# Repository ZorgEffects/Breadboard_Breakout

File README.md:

# Breadboard_Breakout
This is a PCB of a breakout audio board used for audio design on a breadboard.  
It's been made to align with a 1660pt breadboard like this one:  
https://mou.sr/4qExcgZ

# Features:
- 9v regulator. Can be turned off with a jumper.
- 3x jacks in/out/aux for audio/CVs
- Relay bypass between IN/OUT. The relay can be removed with jumper.
- 4x push switches with wiring connection
- 6x screw connectors to fix pots on the boards and wire them to the breadboard
- Filtered Vref = Vcc/2
- Bananas connexion for an external power supply
- Test points for signals (T1 and T2, near the bananas)
- Test points for I/Os (IN/OUT/AUX, right of the jacks)

# Short BOM:
Relay :  
https://www.mouser.fr/ProductDetail/Omron-Electronics/G6K-2P-Y-DC9?qs=wkx8pu8tL7LXpnqEum69xQ%3D%3D  
Push Switch (latch):  
https://www.mouser.fr/ProductDetail/E-Switch/JN2UOANAGX?qs=3Jlm%2Fl9ddLz4b5MH%2B0K8sg%3D%3D&countryCode=DE&currencyCode=EUR  
Switch cap:  
https://www.mouser.fr/ProductDetail/E-Switch/TAG-BLK?qs=sGAEpiMZZMtFyPk3yBMYYOwc5eDcStsDSmqEZ9eg82w%3D  
Pot connector:  
https://www.mouser.fr/ProductDetail/Phoenix-Contact/1935394?qs=%2FbRkJSLTVS%2FBYbus49HMUQ%3D%3D&countryCode=DE&currencyCode=EUR  
Bypass switch:  
https://www.mouser.fr/ProductDetail/Same-Sky/TS14-1212-100-BK-160-SCR-D?qs=t7xnP681wgUxNt1zer%2Bdww%3D%3D  
Jacks:  
https://www.mouser.fr/ProductDetail/Neutrik/NMJ4HCD2?qs=SzdD80gJ2cAr9Xh3wJi7nw%3D%3D  
Terminals 2.54:  
https://www.mouser.fr/ProductDetail/3M-Electronic-Solutions-Division/2324-6121TG?qs=bmCxD588tEjY10%2FzUyHH%2BQ%3D%3D  
https://www.mouser.fr/c/connectors/headers-wire-housings/?contact%20gender=Socket%20(Female)&mounting%20angle=Straight&mounting%20style=Through%20Hole&number%20of%20rows=1%20Row&pitch=2.54%20mm%20(0.1%20in)~~2.54%20mm%2C%205%20mm&row%20spacing=2.54%20mm%20(0.1%20in)&rp=connectors%2Fheaders-wire-housings%7C~Pitch  

The bananas plugs are these:  
https://www.microjpm.com/products/ad27504/

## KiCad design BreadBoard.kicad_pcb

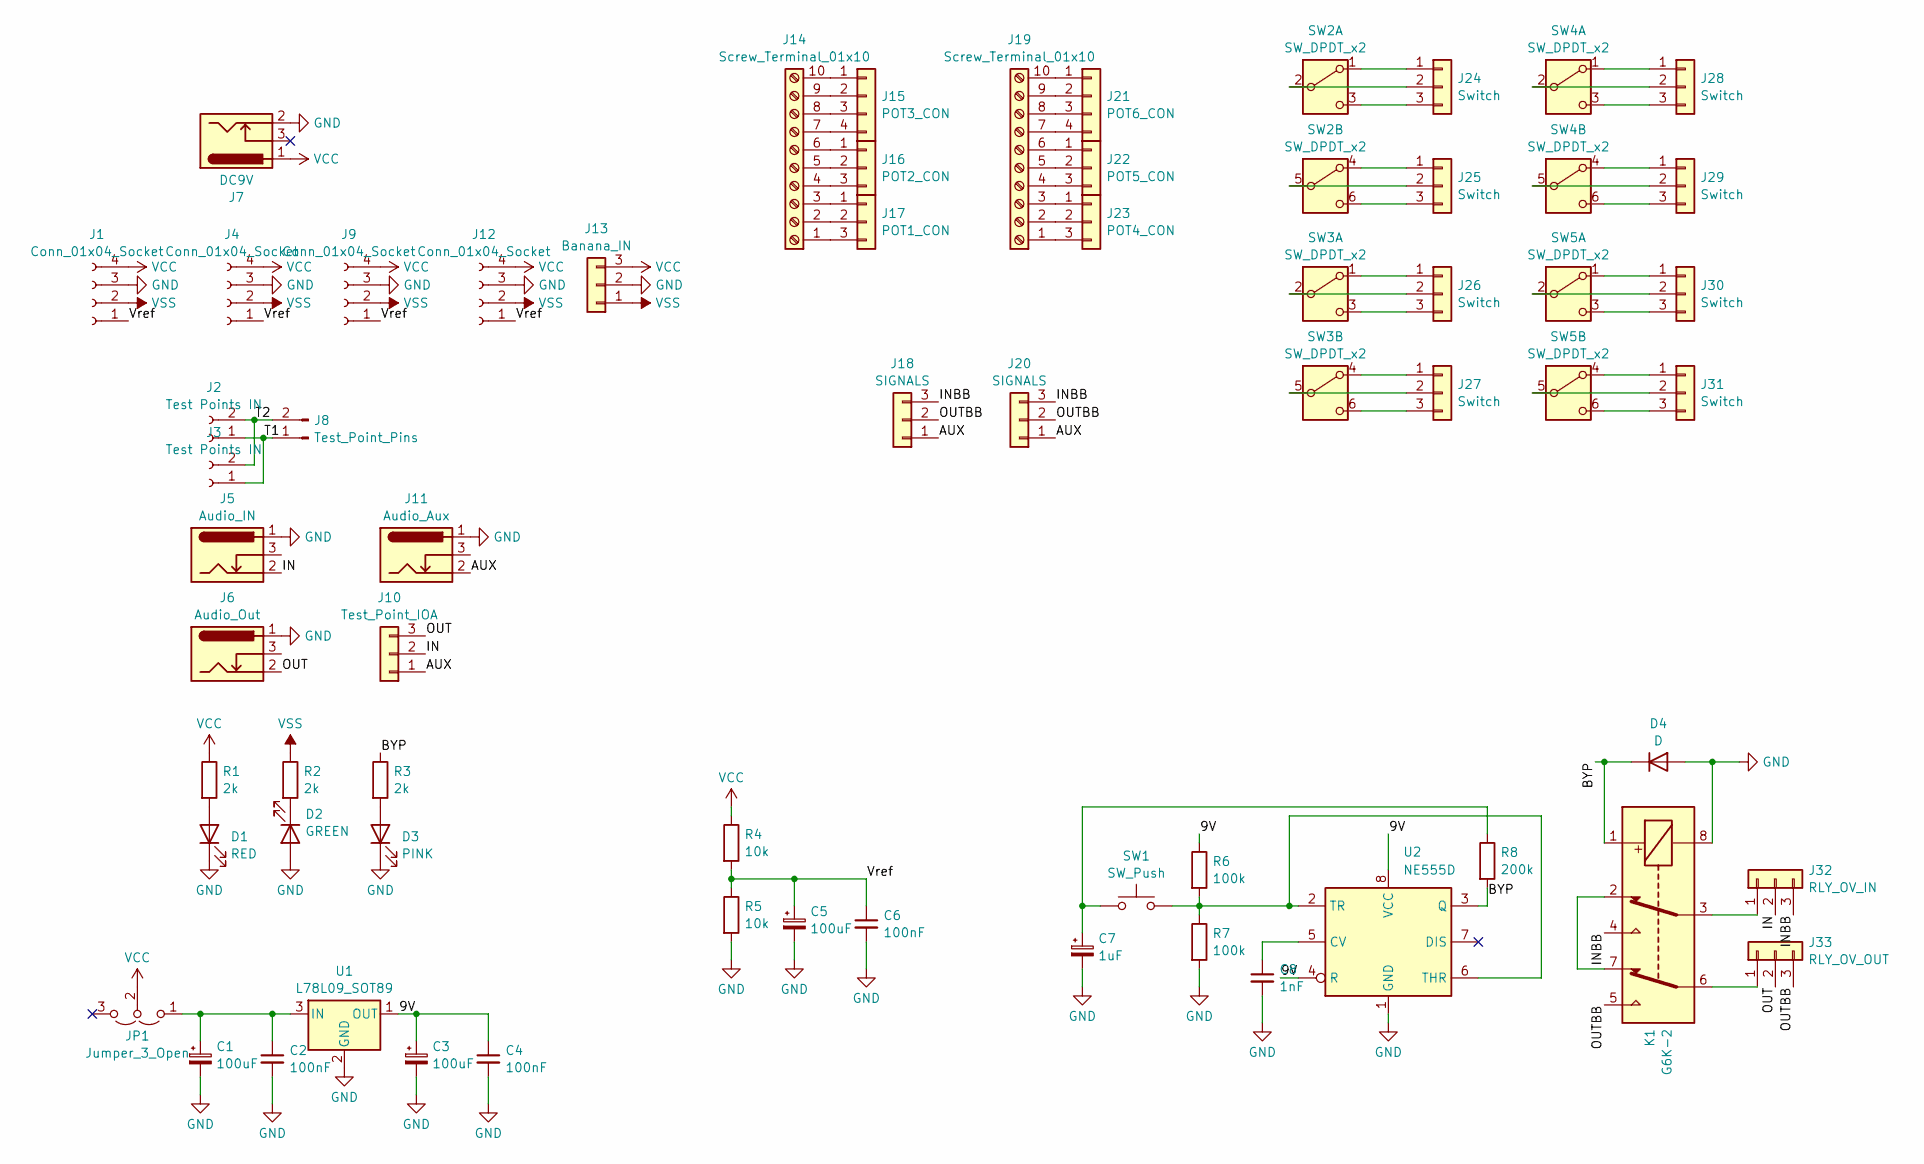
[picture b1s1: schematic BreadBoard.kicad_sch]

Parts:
C1, C3, C5: 100uF; CP_Radial_D6.3mm_P2.50mm
C2, C4, C6: 100nF; C_Rect_L7.0mm_W2.0mm_P5.00mm
C7: 1uF; CP_Radial_D4.0mm_P2.00mm
C8: 1nF; C_Rect_L7.0mm_W2.0mm_P5.00mm
D1: RED; LED_D5.0mm
D2: GREEN; LED_D5.0mm
D3: PINK; LED_D5.0mm
D4: D; D_A-405_P7.62mm_Horizontal
J1, J4, J9, J12: Conn_01x04_Socket; PinSocket_1x04_P2.54mm_Vertical
J2, J3: Test Points IN; PinSocket_1x02_P2.54mm_Vertical
J5: Audio_IN; Jack Neutrik Mono Pins SW
J6: Audio_Out; Jack Neutrik Mono Pins SW
J7: DC9V; Jack DC
J8: Test_Point_Pins; PinHeader_1x02_P2.54mm_Vertical
J10: Test_Point_IOA; PinHeader_1x03_P2.54mm_Vertical
J11: Audio_Aux; Jack Neutrik Mono Pins SW
J13: Banana_IN; PinHeader_1x03_P2.54mm_Vertical
J14, J19: Screw_Terminal_01x10; TerminalBlock_RND_205-00020_1x10_P5.00mm_Horizontal
J15: POT3_CON; PinSocket_1x04_P2.54mm_Vertical
J16: POT2_CON; PinSocket_1x03_P2.54mm_Vertical
J17: POT1_CON; PinSocket_1x03_P2.54mm_Vertical
J18, J20: SIGNALS; PinSocket_1x03_P2.54mm_Vertical
J21: POT6_CON; PinSocket_1x04_P2.54mm_Vertical
J22: POT5_CON; PinSocket_1x03_P2.54mm_Vertical
J23: POT4_CON; PinSocket_1x03_P2.54mm_Vertical
J24, J25, J26, J27, J28, J29, J30, J31: Switch; PinSocket_1x03_P2.54mm_Vertical
J32: RLY_OV_IN; PinHeader_1x03_P2.54mm_Vertical
J33: RLY_OV_OUT; PinHeader_1x03_P2.54mm_Vertical
JP1: Jumper_3_Open; PinHeader_1x03_P2.54mm_Vertical
K1: G6K-2; Relay_DPDT_Omron_G6K-2P-Y
R1, R2, R3: 2k; R_Axial_DIN0207_L6.3mm_D2.5mm_P10.16mm_Horizontal
R4, R5: 10k; R_Axial_DIN0207_L6.3mm_D2.5mm_P10.16mm_Horizontal
R6, R7: 100k; R_Axial_DIN0207_L6.3mm_D2.5mm_P10.16mm_Horizontal
R8: 200k; R_Axial_DIN0207_L6.3mm_D2.5mm_P10.16mm_Horizontal
SW1: SW_Push; SW_PUSH-12mm
SW2, SW3, SW4, SW5: SW_DPDT_x2; DPDT_ESwitch
U1: L78L09_SOT89; DPAK-3
U2: NE555D; SOIC-8_3.9x4.9mm_P1.27mm

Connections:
/9V: C3.1, C4.1, R6.1, U1.1 (OUT), U2.4 (R), U2.8 (VCC)
/AUX: J10.1, J11.2, J18.1, J20.1
/BYP: D4.1 (K), K1.1, R3.1, R8.2, U2.3 (Q)
/IN: J5.2, J10.2, J32.2
/INBB: J18.3, J20.3, J32.3, K1.4
/OUT: J6.2, J10.3, J33.2
/OUTBB: J18.2, J20.2, J33.3, K1.5
/T1: J2.1, J3.1, J8.1
/T2: J2.2, J3.2, J8.2
/Vref: C5.1, C6.1, J1.1, J4.1, J9.1, J12.1, R4.2, R5.1
GND: C1.2, C2.2, C3.2, C4.2, C5.2, C6.2, C7.2, C8.2, D1.1 (K), D2.2 (A), D3.1 (K), D4.2 (A), J1.3, J4.3, J5.1, J6.1, J7.2, J9.3, J11.1, J12.3, J13.2, K1.8, R5.2, R7.2, U1.2 (GND), U2.1 (GND)
unnamed: C7.1, R8.1, SW1.1
unnamed: D1.2 (A), R1.2
unnamed: D2.1 (K), R2.2
unnamed: D3.2 (A), R3.2
unnamed: J14.1, J17.3
unnamed: J14.2, J17.2
unnamed: J14.3, J17.1
unnamed: J14.4, J16.3
unnamed: J14.5, J16.2
unnamed: J14.6, J16.1
unnamed: J14.7, J15.4
unnamed: J14.8, J15.3
unnamed: J14.9, J15.2
unnamed: J14.10, J15.1
unnamed: J19.1, J23.3
unnamed: J19.2, J23.2
unnamed: J19.3, J23.1
unnamed: J19.4, J22.3
unnamed: J19.5, J22.2
unnamed: J19.6, J22.1
unnamed: J19.7, J21.4
unnamed: J19.8, J21.3
unnamed: J19.9, J21.2
unnamed: J19.10, J21.1
unnamed: J24.1, SW2.1 (A)
unnamed: J24.2, SW2.2 (B)
unnamed: J24.3, SW2.3 (C)
unnamed: J25.1, SW2.4 (A)
unnamed: J25.2, SW2.5 (B)
unnamed: J25.3, SW2.6 (C)
unnamed: J26.1, SW3.1 (A)
unnamed: J26.2, SW3.2 (B)
unnamed: J26.3, SW3.3 (C)
unnamed: J27.1, SW3.4 (A)
unnamed: J27.2, SW3.5 (B)
unnamed: J27.3, SW3.6 (C)
unnamed: J28.1, SW4.1 (A)
unnamed: J28.2, SW4.2 (B)
unnamed: J28.3, SW4.3 (C)
unnamed: J29.1, SW4.4 (A)
unnamed: J29.2, SW4.5 (B)
unnamed: J29.3, SW4.6 (C)
unnamed: J30.1, SW5.1 (A)
unnamed: J30.2, SW5.2 (B)
unnamed: J30.3, SW5.3 (C)
unnamed: J31.1, SW5.4 (A)
unnamed: J31.2, SW5.5 (B)
unnamed: J31.3, SW5.6 (C)
unnamed: J32.1, K1.3
unnamed: J33.1, K1.6
unnamed: C1.1, C2.1, JP1.1 (A), U1.3 (IN)
unnamed: K1.2, K1.7
unnamed: C8.1, U2.5 (CV)
unnamed: R6.2, R7.1, SW1.2, U2.2 (TR), U2.6 (THR)
VCC: J1.4, J4.4, J7.1, J9.4, J12.4, J13.3, JP1.2 (C), R1.1, R4.1
VSS: J1.2, J4.2, J9.2, J12.2, J13.1, R2.1

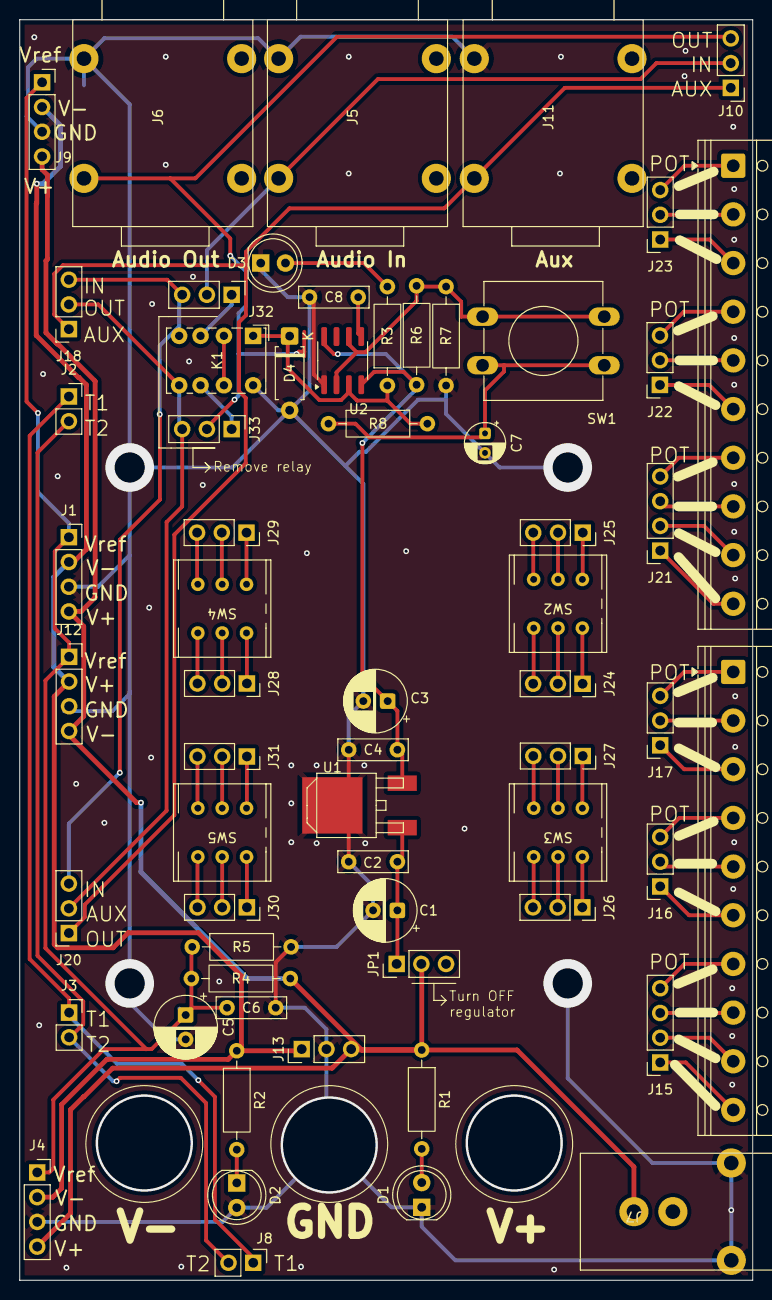
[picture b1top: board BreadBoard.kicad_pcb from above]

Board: 2 copper layers, 75.3 x 129.5 mm, 62 parts (0 on the bottom side), 67 nets.
